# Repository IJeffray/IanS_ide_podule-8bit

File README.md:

# IDE podule 8 bit

8-bit IDE podule for Acorn machines (A3000, A3010, A3020 & A4000). It also includes a header for a CH376 USB module compatible with USBFS.

Compatibe with the interface number 3 version of ZIDEFS - https://www.zeridajh.org/software/zidefs/index.html

Flash can be programmed in-situ, so the chip can be soldered on-board without a socket.

More details on USBFS and a stand-alone USBFS podule here - https://codeberg.org/IanS/ch376_podule

The flash chip (SST39SF010) can be used in its entirety as a single 128K block with both switches turned on. It make more sense to treat it as four 32K chunks to allow the alternative version of the ZIDEFS software to be used. Using the different versions (ZIDEFS/IDEFS/SIDEFS) allows multiple podules to be installed in a single machine. Note that the ZIDEFS partitioning, deviceid and formatting tools only work with the ZIDEFS version. Multiple podules is only likely to be possible on an A3000 using both the internal and external podules connectors.

PCB

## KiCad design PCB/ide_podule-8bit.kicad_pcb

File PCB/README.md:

# ide podule 8bit

These are the KiCad (version 8) files for the 8-bit ide podule.

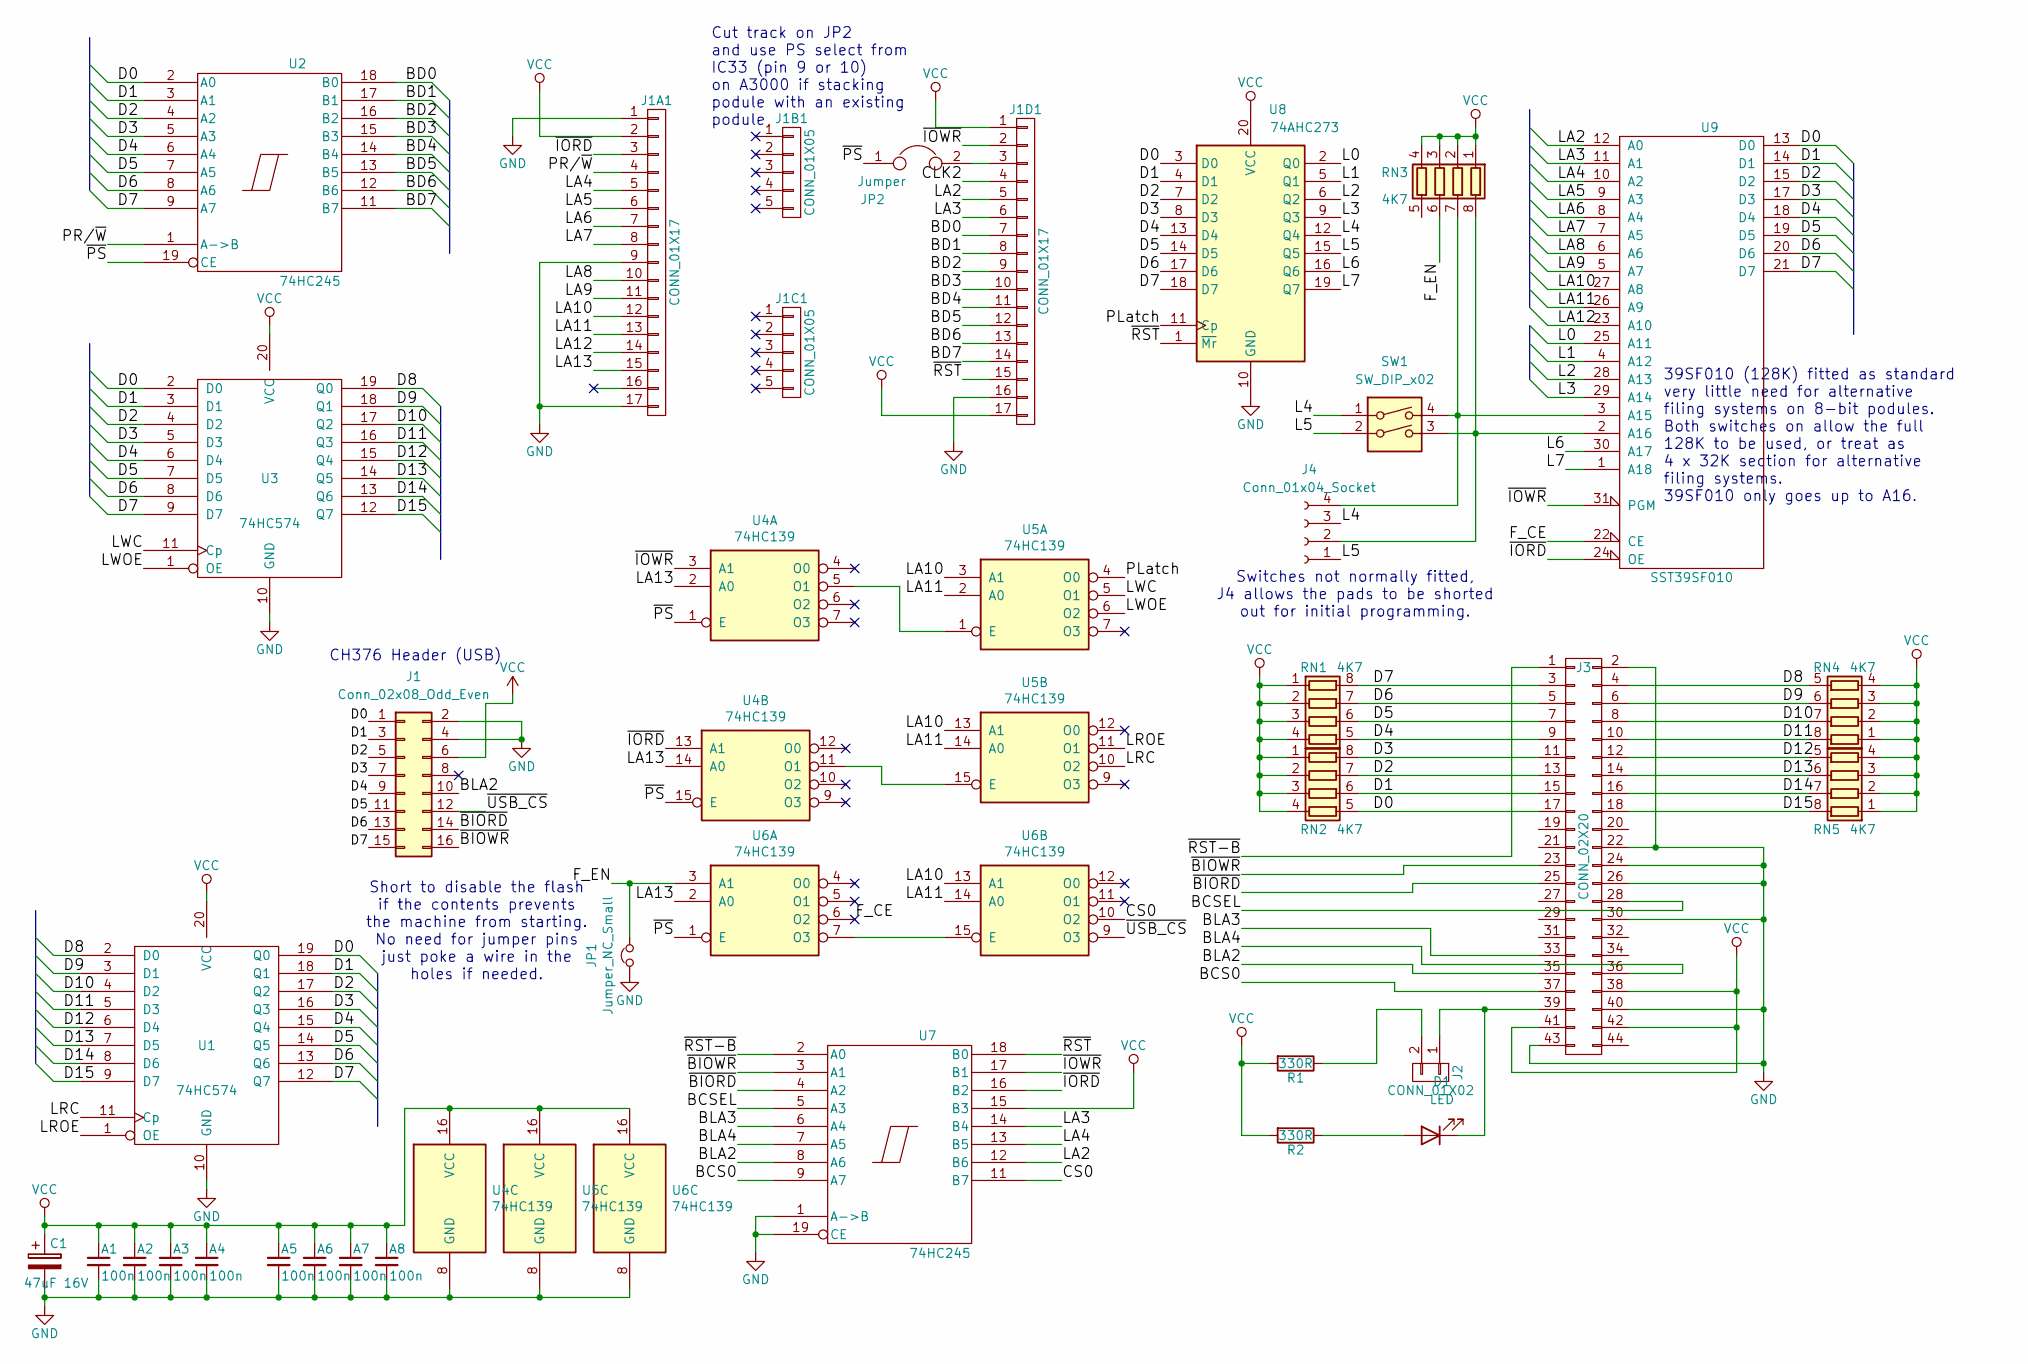
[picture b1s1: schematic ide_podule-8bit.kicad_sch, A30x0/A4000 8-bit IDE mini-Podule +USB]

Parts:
A1, A2, A3, A4, A5, A6, A7, A8: 100n; C_1206_3216Metric_Pad1.33x1.80mm_HandSolder
C1: 47uF 16V; CP_EIA-6032-20_AVX-F_Pad2.25x2.35mm_HandSolder
D1: LED; LED_1206_3216Metric_Pad1.42x1.75mm_HandSolder
J1: Conn_02x08_Odd_Even; CH376-mod
J1A1, J1D1: CONN_01X17; PinHeader_1x17_P2.54mm_Vertical
J1B1, J1C1: CONN_01X05; PinHeader_1x05_P2.54mm_Vertical
J2: CONN_01X02; PinHeader_1x02_P2.54mm_Vertical
J3: CONN_02X20; PinHeader_2x22_P2.00mm_Vertical
J4: Conn_01x04_Socket; 4 way edge
JP1: Jumper_NC_Small; PinHeader_1x02
JP2: Jumper; PinHeader_1x02-linked
R1, R2: 330R; R_1206_3216Metric_Pad1.30x1.75mm_HandSolder
RN1, RN2, RN3, RN4, RN5: 4K7; R_Array_Concave_4x0603
SW1: SW_DIP_x02; DIP-4_W7.62mm_Socket
U1, U3: 74HC574; SOIC-20W_7.5x12.8mm_P1.27mm
U2, U7: 74HC245; SOIC-20W_7.5x12.8mm_P1.27mm
U4, U5, U6: 74HC139; SOIC-16_3.9x9.9mm_P1.27mm
U8: 74AHC273; SOIC-20W_7.5x12.8mm_P1.27mm
U9: SST39SF010; PLCC-32_11.4x14.0mm_P1.27mm

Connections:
/BCS0: J3.37, U7.9 (A7)
/BCSEL: J3.28, U7.5 (A3)
/BD0: J1D1.7, U2.18 (B0)
/BD1: J1D1.8, U2.17 (B1)
/BD2: J1D1.9, U2.16 (B2)
/BD3: J1D1.10, U2.15 (B3)
/BD4: J1D1.11, U2.14 (B4)
/BD5: J1D1.12, U2.13 (B5)
/BD6: J1D1.13, U2.12 (B6)
/BD7: J1D1.14, U2.11 (B7)
/BLA2: J1.10, J3.35, U7.8 (A6)
/BLA3: J3.33, U7.6 (A4)
/BLA4: J3.36, U7.7 (A5)
/CLK2: J1D1.4
/CS0: U6.10 (O2), U7.11 (B7)
/D0: J1.1, J3.17, RN2.5 (R4.2), U1.19 (Q0), U2.2 (A0), U3.2 (D0), U8.3 (D0), U9.13 (D0)
/D1: J1.3, J3.15, RN2.6 (R3.2), U1.18 (Q1), U2.3 (A1), U3.3 (D1), U8.4 (D1), U9.14 (D1)
/D2: J1.5, J3.13, RN2.7 (R2.2), U1.17 (Q2), U2.4 (A2), U3.4 (D2), U8.7 (D2), U9.15 (D2)
/D3: J1.7, J3.11, RN2.8 (R1.2), U1.16 (Q3), U2.5 (A3), U3.5 (D3), U8.8 (D3), U9.17 (D3)
/D4: J1.9, J3.9, RN1.5 (R4.2), U1.15 (Q4), U2.6 (A4), U3.6 (D4), U8.13 (D4), U9.18 (D4)
/D5: J1.11, J3.7, RN1.6 (R3.2), U1.14 (Q5), U2.7 (A5), U3.7 (D5), U8.14 (D5), U9.19 (D5)
/D6: J1.13, J3.5, RN1.7 (R2.2), U1.13 (Q6), U2.8 (A6), U3.8 (D6), U8.17 (D6), U9.20 (D6)
/D7: J1.15, J3.3, RN1.8 (R1.2), U1.12 (Q7), U2.9 (A7), U3.9 (D7), U8.18 (D7), U9.21 (D7)
/D8: J3.4, RN4.5 (R4.2), U1.2 (D0), U3.19 (Q0)
/D9: J3.6, RN4.6 (R3.2), U1.3 (D1), U3.18 (Q1)
/D10: J3.8, RN4.7 (R2.2), U1.4 (D2), U3.17 (Q2)
/D11: J3.10, RN4.8 (R1.2), U1.5 (D3), U3.16 (Q3)
/D12: J3.12, RN5.5 (R4.2), U1.6 (D4), U3.15 (Q4)
/D13: J3.14, RN5.6 (R3.2), U1.7 (D5), U3.14 (Q5)
/D14: J3.16, RN5.7 (R2.2), U1.8 (D6), U3.13 (Q6)
/D15: J3.18, RN5.8 (R1.2), U1.9 (D7), U3.12 (Q7)
/F_CE: U6.6 (O2), U9.22 (CE)
/F_EN: JP1.2, RN3.6 (R3.2), U6.3 (A1)
/L0: U8.2 (Q0), U9.25 (A11)
/L1: U8.5 (Q1), U9.4 (A12)
/L2: U8.6 (Q2), U9.28 (A13)
/L3: U8.9 (Q3), U9.29 (A14)
/L4: J4.3, SW1.1, U8.12 (Q4)
/L5: J4.1, SW1.2, U8.15 (Q5)
/L6: U8.16 (Q6), U9.30 (A17)
/L7: U8.19 (Q7), U9.1 (A18)
/LA2: J1D1.5, U7.12 (B6), U9.12 (A0)
/LA3: J1D1.6, U7.14 (B4), U9.11 (A1)
/LA4: J1A1.5, U7.13 (B5), U9.10 (A2)
/LA5: J1A1.6, U9.9 (A3)
/LA6: J1A1.7, U9.8 (A4)
/LA7: J1A1.8, U9.7 (A5)
/LA8: J1A1.10, U9.6 (A6)
/LA9: J1A1.11, U9.5 (A7)
/LA10: J1A1.12, U5.3 (A1), U5.13 (A1), U6.13 (A1), U9.27 (A8)
/LA11: J1A1.13, U5.2 (A0), U5.14 (A0), U6.14 (A0), U9.26 (A9)
/LA12: J1A1.14, U9.23 (A10)
/LA13: J1A1.15, U4.2 (A0), U4.14 (A0), U6.2 (A0)
/LRC: U1.11 (Cp), U5.10 (O2)
/LROE: U1.1 (OE), U5.11 (O1)
/LWC: U3.11 (Cp), U5.5 (O1)
/LWOE: U3.1 (OE), U5.6 (O2)
/PLatch: U5.4 (O0), U8.11 (Cp)
/PR/~W: J1A1.4, U2.1 (A->B)
/~BIORD: J1.14, J3.25, U7.4 (A2)
/~BIOWR: J1.16, J3.23, U7.3 (A1)
/~IORD: J1A1.3, U4.13 (A1), U7.16 (B2), U9.24 (OE)
/~IOWR: J1D1.2, U4.3 (A1), U7.17 (B1), U9.31 (PGM)
/~PS: JP2.1, U2.19 (CE), U4.1 (E), U4.15 (E), U6.1 (E)
/~RST-B: J3.1, U7.2 (A0)
/~RST: J1D1.15, U7.18 (B0), U8.1 (~Mr)
/~USB_CS: J1.12, U6.9 (O3)
GND: A1.2, A2.2, A3.2, A4.2, A5.2, A6.2, A7.2, A8.2, C1.2, J1.2, J1.4, J1A1.1, J1A1.9, J1A1.17, J1D1.16, J3.2, J3.22, J3.24, J3.26, J3.30, J3.40, J3.43, JP1.1, U1.10 (GND), U2.10 (GND), U3.10 (GND), U4.8 (GND), U5.8 (GND), U6.8 (GND), U7.1 (A->B), U7.10 (GND), U7.19 (CE), U8.10 (GND), U9.16 (GND)
unnamed: D1.2 (A), R2.1
unnamed: D1.1 (K), J2.1, J3.39
unnamed: J1D1.3, JP2.2
unnamed: J2.2, R1.1
unnamed: J4.2, RN3.8 (R1.2), SW1.3, U9.2 (A16)
unnamed: J4.4, RN3.7 (R2.2), SW1.4, U9.3 (A15)
unnamed: U4.5 (O1), U5.1 (E)
unnamed: U4.11 (O1), U5.15 (E)
unnamed: U6.7 (O3), U6.15 (E)
VCC: A1.1, A2.1, A3.1, A4.1, A5.1, A6.1, A7.1, A8.1, C1.1, J1.6, J1A1.2, J1D1.1, J1D1.17, J3.38, J3.41, J3.42, R1.2, R2.2, RN1.1 (R1.1), RN1.2 (R2.1), RN1.3 (R3.1), RN1.4 (R4.1), RN2.1 (R1.1), RN2.2 (R2.1), RN2.3 (R3.1), RN2.4 (R4.1), RN3.1 (R1.1), RN3.2 (R2.1), RN3.3 (R3.1), RN3.4 (R4.1), RN4.1 (R1.1), RN4.2 (R2.1), RN4.3 (R3.1), RN4.4 (R4.1), RN5.1 (R1.1), RN5.2 (R2.1), RN5.3 (R3.1), RN5.4 (R4.1), U1.20 (VCC), U2.20 (VCC), U3.20 (VCC), U4.16 (VCC), U5.16 (VCC), U6.16 (VCC), U7.15 (B3), U7.20 (VCC), U8.20 (VCC), U9.32 (VCC)

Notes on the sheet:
Switches not normally fitted, J4 allows the pads to be shorted out for initial programming.
39SF010 (128K) fitted as standard very little need for alternative filing systems on 8-bit podules. Both switches on allow the full 128K to be used, or treat as 4 x 32K section for alternative filing systems. 39SF010 only goes up to A16.
Cut track on JP2 and use PS select from IC33 (pin 9 or 10) on A3000 if stacking podule with an existing podule
CH376 Header (USB)
Short to disable the flash if the contents prevents the machine from starting. No need for jumper pins just poke a wire in the holes if needed.

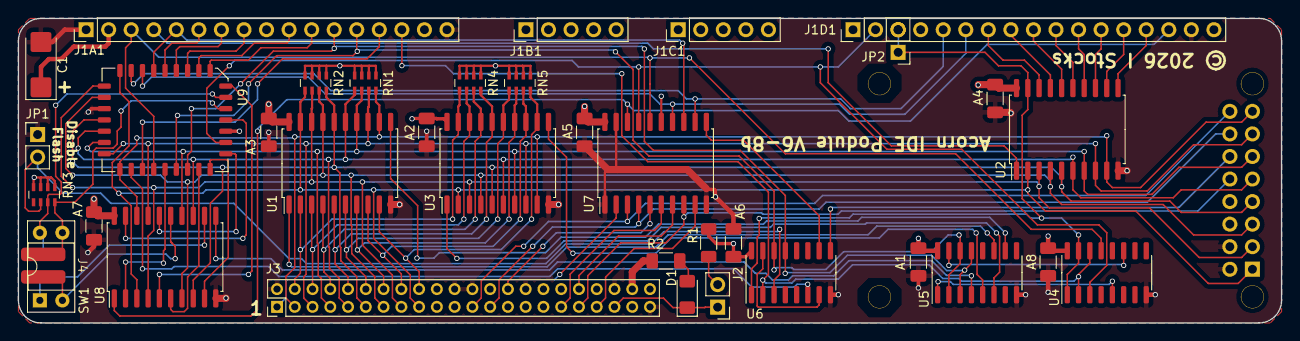
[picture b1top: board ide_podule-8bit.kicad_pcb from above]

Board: 4 copper layers, 142.2 x 34.3 mm, 37 parts (1 on the bottom side), 77 nets.

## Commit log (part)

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2026-04-19 initial version
2026-04-21 add software

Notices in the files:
PCB/ide_podule-8bit.kicad_pcb:
© 2026 I Stocks
